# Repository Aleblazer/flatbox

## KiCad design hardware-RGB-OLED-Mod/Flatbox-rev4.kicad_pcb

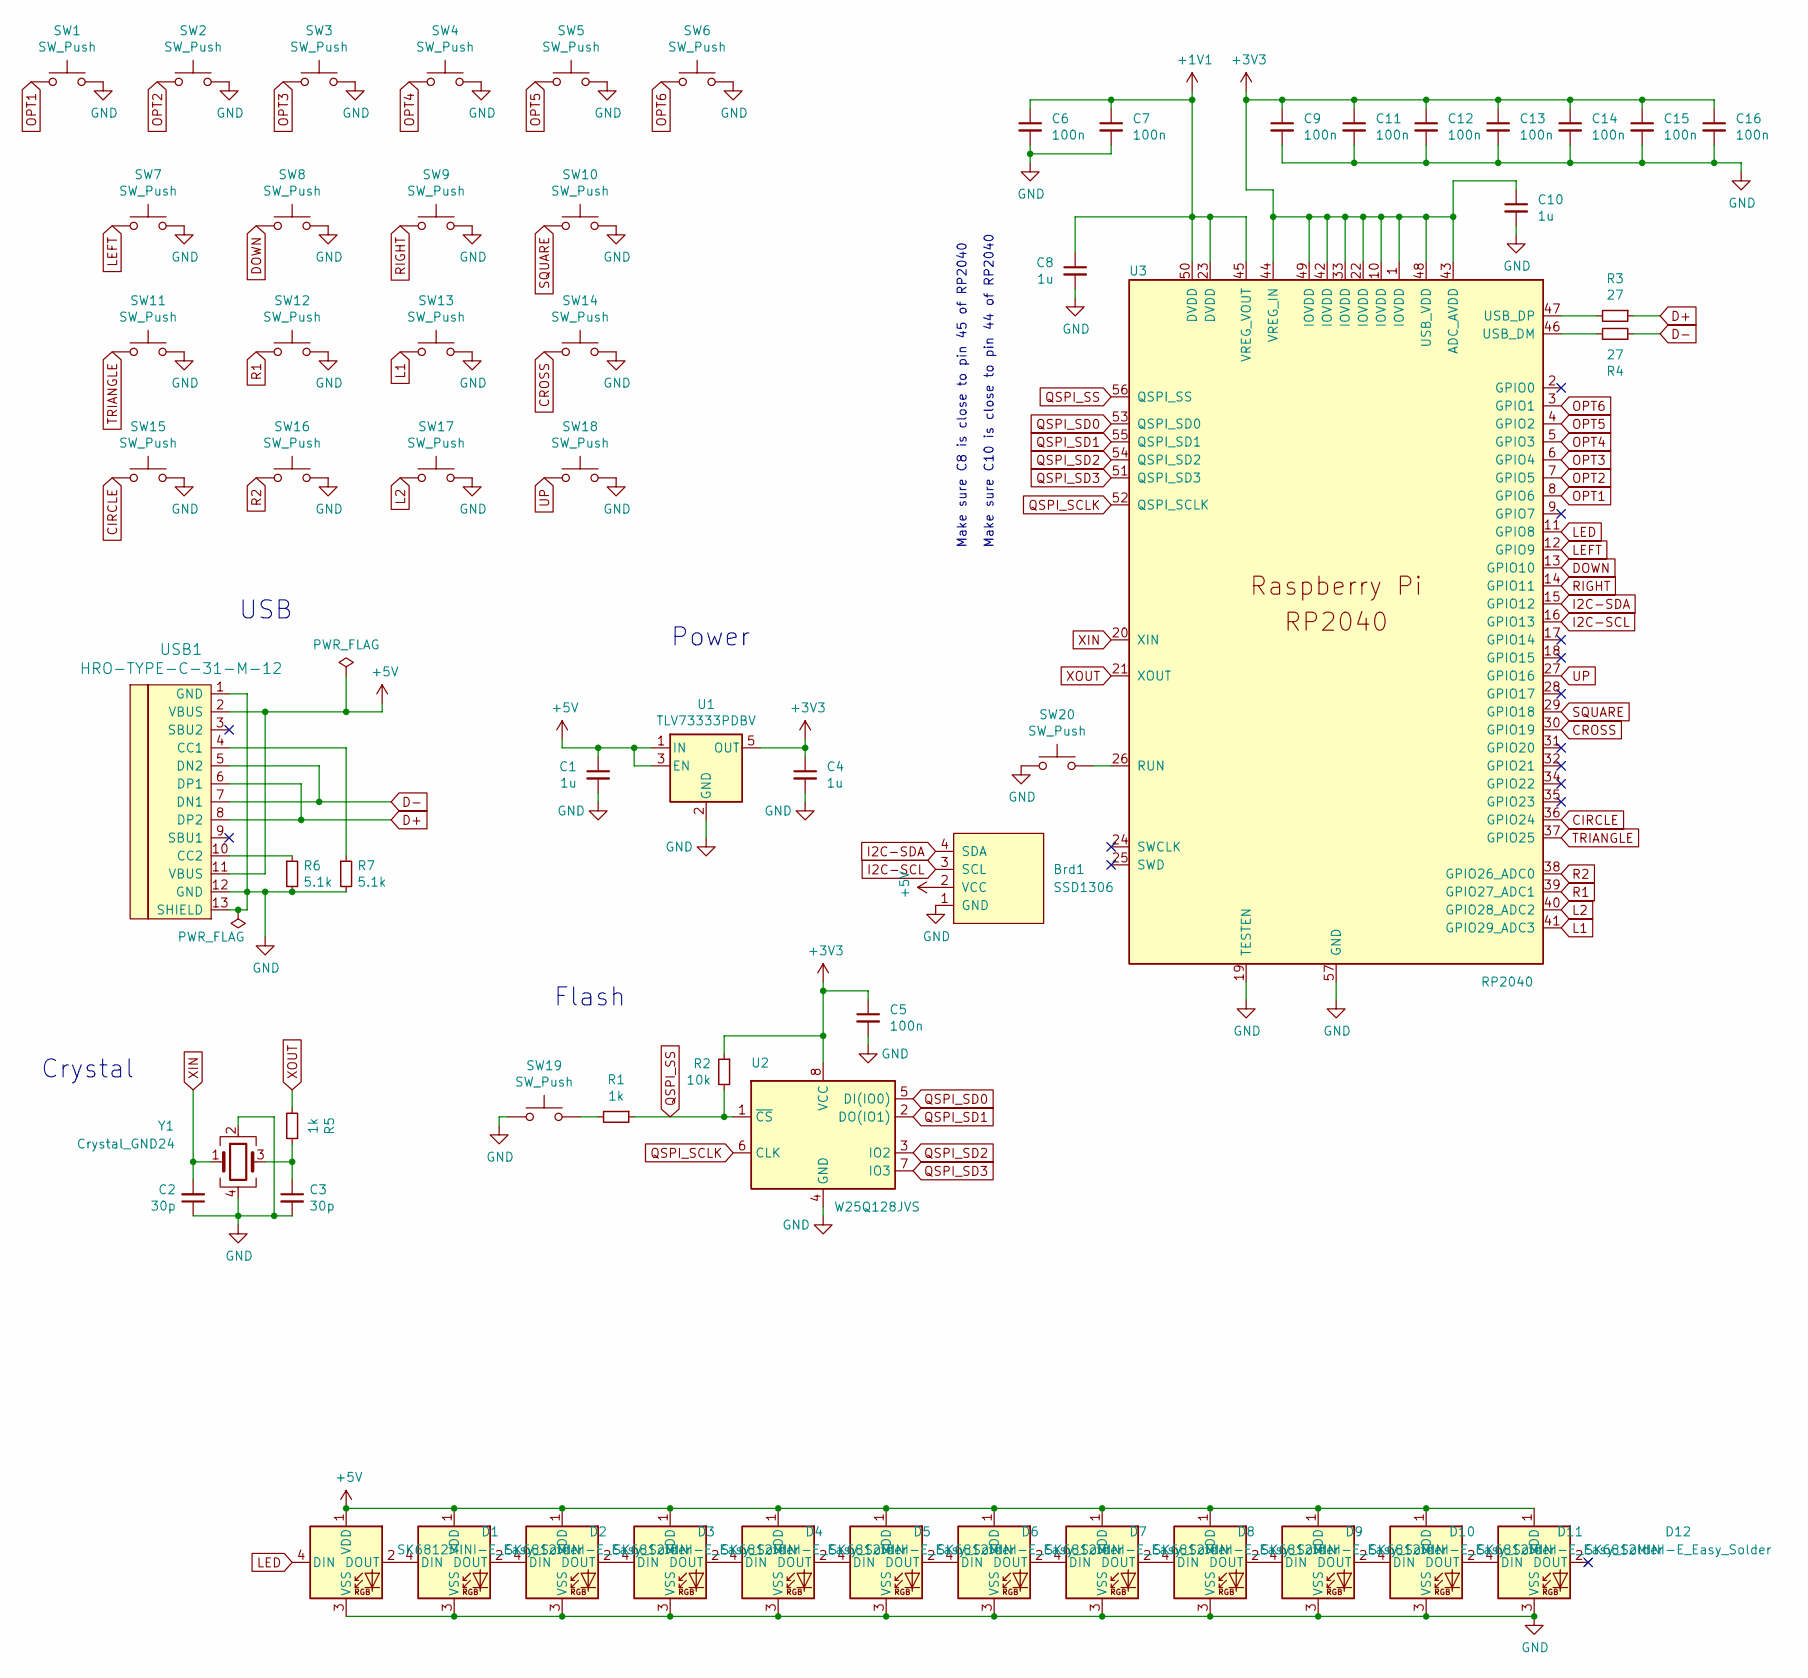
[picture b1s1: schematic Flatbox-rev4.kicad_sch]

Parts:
Brd1: SSD1306; 128x64OLED
C1, C4, C8, C10: 1u; C_0402_1005Metric; LCSC C52923
C2, C3: 30p; C_0402_1005Metric; LCSC C1570
C5, C6, C7, C9, C11, C12, C13, C14, C15, C16: 100n; C_0402_1005Metric; LCSC C1525
D1, D2, D3, D4, D5, D6, D7, D8, D9, D10, D11, D12: SK6812MINI-E_Easy_Solder; YS-SK6812MINI-E-SingleSide
R1, R5: 1k; R_0402_1005Metric; LCSC C11702
R2: 10k; R_0402_1005Metric; LCSC C25744
R3, R4: 27; R_0402_1005Metric; LCSC C138021
R6, R7: 5.1k; R_0402_1005Metric; LCSC C25905
SW1, SW2, SW3, SW4, SW5, SW6: SW_Push; SW_PUSH_6mm_H5mm
SW7, SW8, SW9, SW10, SW11, SW12, SW13, SW14, SW15, SW16, SW17, SW18: SW_Push; Kailh_socket_MX-ChocV1
SW19, SW20: SW_Push; SW_SPST_Omron_B3FS-100xP; LCSC C271750
U1: TLV73333PDBV; SOT-23-5; LCSC C134139
U2: W25Q128JVS; SOIC-8_5.23x5.23mm_P1.27mm; LCSC C97521
U3: RP2040; RP2040-QFN-56; LCSC C2040
USB1: HRO-TYPE-C-31-M-12; HRO-TYPE-C-31-M-12-Assembly; LCSC C165948
Y1: Crystal_GND24; Crystal_SMD_3225-4Pin_3.2x2.5mm; LCSC C9002

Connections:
+1V1: C6.1, C7.1, C8.1, U3.23 (DVDD), U3.45 (VREG_VOUT), U3.50 (DVDD)
+3V3: C4.1, C5.1, C9.1, C10.1, C11.1, C12.1, C13.1, C14.1, C15.1, C16.1, R2.1, U1.5 (OUT), U2.8 (VCC), U3.1 (IOVDD), U3.10 (IOVDD), U3.22 (IOVDD), U3.33 (IOVDD), U3.42 (IOVDD), U3.43 (ADC_AVDD), U3.44 (VREG_IN), U3.48 (USB_VDD), U3.49 (IOVDD)
+5V: Brd1.2 (VCC), C1.1, D1.1 (VDD), D2.1 (VDD), D3.1 (VDD), D4.1 (VDD), D5.1 (VDD), D6.1 (VDD), D7.1 (VDD), D8.1 (VDD), D9.1 (VDD), D10.1 (VDD), D11.1 (VDD), D12.1 (VDD), U1.1 (IN), U1.3 (EN), USB1.2 (VBUS), USB1.11 (VBUS); also elsewhere on the board
CIRCLE: SW15.1, U3.36 (GPIO24)
CROSS: SW14.1, U3.30 (GPIO19)
D+: R3.1, USB1.6 (DP1), USB1.8 (DP2)
D-: R4.1, USB1.5 (DN2), USB1.7 (DN1)
DOWN: SW8.1, U3.13 (GPIO10)
GND: Brd1.1 (GND), C1.2, C2.1, C3.2, C4.2, C5.2, C6.2, C7.2, C8.2, C9.2, C10.2, C11.2, C12.2, C13.2, C14.2, C15.2, C16.2, D1.3 (VSS), D2.3 (VSS), D3.3 (VSS), D4.3 (VSS), D5.3 (VSS), D6.3 (VSS), D7.3 (VSS), D8.3 (VSS), D9.3 (VSS), D10.3 (VSS), D11.3 (VSS), D12.3 (VSS), R6.2, R7.2, SW1.2, SW2.2, SW3.2, SW4.2, SW5.2, SW6.2, SW7.2, SW8.2, SW9.2, SW10.2, SW11.2, SW12.2, SW13.2, SW14.2, SW15.2, SW16.2, SW17.2, SW18.2, SW19.1, SW20.1, U1.2 (GND), U2.4 (GND), U3.19 (TESTEN), U3.57 (GND), USB1.1 (GND), USB1.12 (GND), USB1.13 (SHIELD), Y1.2, Y1.4; also elsewhere on the board
I2C-SCL: Brd1.3 (SCL), U3.16 (GPIO13); also elsewhere on the board
I2C-SDA: Brd1.4 (SDA), U3.15 (GPIO12); also elsewhere on the board
L1: SW13.1, U3.41 (GPIO29_ADC3)
L2: SW17.1, U3.40 (GPIO28_ADC2)
LED: D1.4 (DIN), U3.11 (GPIO8)
LEFT: SW7.1, U3.12 (GPIO9)
unnamed: C3.1, R5.1, Y1.3
unnamed: D1.2 (DOUT), D2.4 (DIN)
unnamed: D2.2 (DOUT), D3.4 (DIN)
unnamed: D3.2 (DOUT), D4.4 (DIN)
unnamed: D4.2 (DOUT), D5.4 (DIN)
unnamed: D5.2 (DOUT), D6.4 (DIN)
unnamed: D6.2 (DOUT), D7.4 (DIN)
unnamed: D7.2 (DOUT), D8.4 (DIN)
unnamed: D8.2 (DOUT), D9.4 (DIN)
unnamed: D10.2 (DOUT), D11.4 (DIN)
unnamed: D9.2 (DOUT), D10.4 (DIN)
unnamed: D11.2 (DOUT), D12.4 (DIN)
unnamed: R1.2, SW19.2
unnamed: R3.2, U3.47 (USB_DP)
unnamed: R4.2, U3.46 (USB_DM)
unnamed: R6.1, USB1.10 (CC2)
unnamed: R7.1, USB1.4 (CC1)
unnamed: SW20.2, U3.26 (RUN)
OPT1: SW1.1, U3.8 (GPIO6)
OPT2: SW2.1, U3.7 (GPIO5)
OPT3: SW3.1, U3.6 (GPIO4)
OPT4: SW4.1, U3.5 (GPIO3)
OPT5: SW5.1, U3.4 (GPIO2)
OPT6: SW6.1, U3.3 (GPIO1)
QSPI_SCLK: U2.6 (CLK), U3.52 (QSPI_SCLK)
QSPI_SD0: U2.5 (DI(IO0)), U3.53 (QSPI_SD0)
QSPI_SD1: U2.2 (DO(IO1)), U3.55 (QSPI_SD1)
QSPI_SD2: U2.3 (IO2), U3.54 (QSPI_SD2)
QSPI_SD3: U2.7 (IO3), U3.51 (QSPI_SD3)
QSPI_SS: R1.1, R2.2, U2.1 (~CS), U3.56 (QSPI_SS)
R1: SW12.1, U3.39 (GPIO27_ADC1)
R2: SW16.1, U3.38 (GPIO26_ADC0)
RIGHT: SW9.1, U3.14 (GPIO11)
SQUARE: SW10.1, U3.29 (GPIO18)
TRIANGLE: SW11.1, U3.37 (GPIO25)
UP: SW18.1, U3.27 (GPIO16)
XIN: C2.2, U3.20 (XIN), Y1.1
XOUT: R5.2, U3.21 (XOUT)

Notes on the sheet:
USB
Crystal
Make sure C8 is close to pin 45 of RP2040
Flash
Make sure C10 is close to pin 44 of RP2040
Power

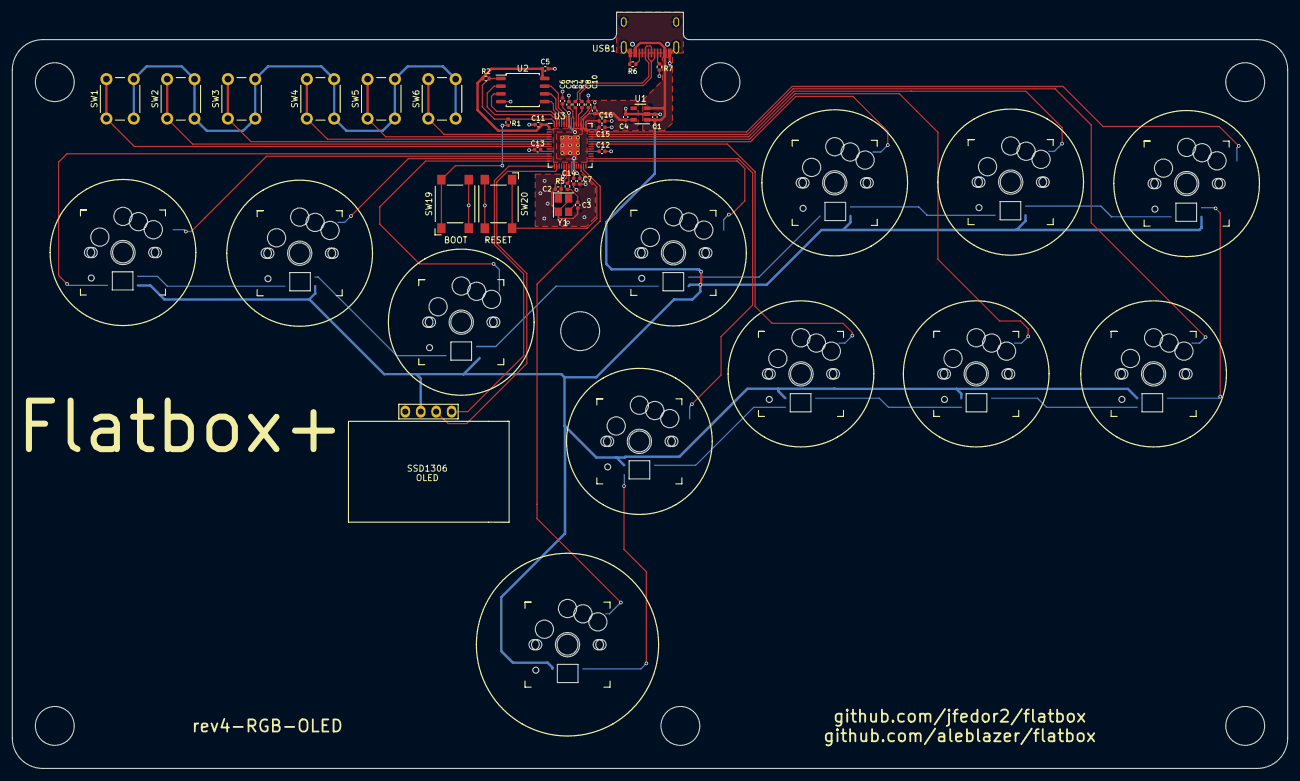
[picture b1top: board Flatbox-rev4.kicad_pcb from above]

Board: 2 copper layers, 209.9 x 124.4 mm, 61 parts (0 on the bottom side), 53 nets.

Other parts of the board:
OLED: SSD1306; 128x64OLED

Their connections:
+5V: OLED.2 (VCC); also elsewhere on the board
GND: OLED.1 (GND); also elsewhere on the board
I2C-SCL: OLED.3 (SCL); also elsewhere on the board
I2C-SDA: OLED.4 (SDA); also elsewhere on the board

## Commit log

2022-11-07 Added hardware-RGB-OLED-Mod
    Added folder and Kicad files for an updated version with combo MX/Choc hotswap footprints, Per key RGB and an OLED.
2022-11-07 Added Gerber files
    Added Gerber files for production, PCBs on order from JLCPCB to confirm functionality.
2022-11-07 Added Case files
    Added modified case STLs
2022-11-18 Updated Top Case for OLED
    Shifted OLED window down 1.5mm
